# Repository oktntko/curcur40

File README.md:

# curcur40

**curcur40** は、[Corne Keyboard (crkbd v4)](https://github.com/foostan/crkbd) をベースに、Kailh Choc V2（`CPG1353`）ロープロファイルスイッチ専用の **40キー左右分割レイアウト**、右手親指内側の **$\varnothing 25\,\text{mm}$ 光学式トラックボール（`PMW3360DM-T2QU` 低プロファイル分離センサーサブ基板）**、および右手人差し指内側の **アンダープレート 1ピース一体軸パッシブ磁気慣性ホイール（`45# Steel` 削り出しフライホイール ＋ 右メイン基板 PCBA 直実装 `TMAG5273` 3Dホール磁気センサ）** を統合し、筐体全体を **真鍮ヒートセットインサート × 統一 `M2 × 6.0mm` ネジ（100% 密閉・底面穴なしケース）** で構築したカスタム分割エルゴノミクスキーボードです。

---

## 主な特徴 (Key Features)

- **40キー + 25mm トラックボール + アンダープレート一体軸パッシブ磁気慣性ホイール**:
  - **左手 (21キー)**: メイン $3\times 5$ (15キー) ＋ 内側縦2キー (`EXSW1`, `EXSW2`) ＋ 親指4キー (`SW1`, `SW8`, `SW9`, `EXSW3`)
  - **右手 (19キー + 2デバイス)**: メイン $3\times 5$ (15キー) ＋ 内側下段1キー (`rEXSW2`) ＋ 親指外側3キー (`rSW1`, `rSW8`, `rSW9`) ＋ **アンダープレート一体軸パッシブ磁気慣性ホイール（静音中クリック付）** ＋ **$\varnothing 25\,\text{mm}$ トラックボール (`PMW3360DM-T2QU` + `LM19-LSI`)**
- **接着剤ゼロ・シムゼロ・手配線ゼロ・カバー不要の「アンダープレート 1ピース一体軸パッシブ磁気慣性ホイール」**:
  - 指当たりが広く心地よい **外径 $\varnothing 22.00 \times \text{幅 } 6.50\,\text{mm}$ リム（外周24フルート溝、南側キー `rEXSW2` と左右中心軸完全一致）**・$\varnothing 2.90\,\text{mm}$ 内輪当たり段付き肩・$\varnothing 1.98\,\text{mm}$ ジャーナル＆Dカット軸を単一鋼材から削り出した **1ピース `45# Steel`（無電解ニッケルめっき）フライホイール（[`steel-flywheel.step`](./cases/inertia_wheel/steel-flywheel.step), $19.31\,\text{g}$, $J \approx 1160\,\text{g}\cdot\text{mm}^2$）** と脱脂ミニチュアベアリング **`DDL-520ZZ`**（Cクリップスナップイン保持）により、シムリング調整なしで圧倒的な慣性フリースピンと剛性を実現。
  - 回転軸をプレート下（$Z = -6.90\,\text{mm}$）に沈めることで、大径 $\varnothing 22.00\,\text{mm}$ ホイールでありながら頂点高さを **$Z = +4.10\,\text{mm}$（Choc V2 キーキャップ天面 $+3.60\,\text{mm}$ 比わずか $+0.50\,\text{mm}$）** に抑え、トッププレート開口をカバー不要のシンプルな角丸長穴（$7.70 \times 22.00\,\text{mm}$）に集約。
  - 角度検出には右メイン基板 `B.Cu` へ PCBA 自動実装された 3軸リニアホールIC **`rU6`（`TMAG5273A1QDBVR`）**、中クリックには基板直付けの静音スイッチ **`rEXSW1`（`Kailh Square Silent`）** を採用し、さらに `#03` シーソーロッカーと `#04` クレードルを **Cクリップスナップインヒンジ（抱き角 $239^\circ$）** で機械連結（**ホイール用サブ基板・JST SH コネクタ・手配線ハーネスは完全廃止**）。南ボスの鉄製 `M2×6.0mm` ネジ先端に自己磁力で吸着させた $\varnothing 2\times 2\,\text{mm}$ ネオジム磁石（`NE280`）と強磁性スチールホイールの24溝により、接着剤も鋼球ハブも使わずにノッチ強弱を無段階調整可能。
- **全19箇所 真鍮ヒートセットインサート ＆ 統一 `M2 × 6.0mm` ネジ（左右完全対称キー谷間 $\varnothing 5.20\,\text{mm}$ フラットボス・USB-C 内壁基板受け棚・スイッチ嵌合トッププレート ＆ 100% 密閉フラット底面ケース）**:
  - 旧来の `5.50mm` スペーサーおよびケース底面ザグリ穴を全面廃止し、キーボード全体の全19箇所（左手キー谷間 `L1`〜`L6` 6箇所 ＋ 右手キー谷間 `R1`〜`R6` 6箇所 ＋ トラックボールカップ `TB1`〜`TB4` 4箇所 ＋ ホイールクレードル `WC1`/`WC2` 2箇所 ＋ ホイール磁力調整 1箇所）すべてを **`M2 × L=3.0 × OD=3.2mm` 真鍮ヒートセットインサート（19個）** と **同一サイズの `M2 × 6.0mm` ネジ（19本）** に完全統一。
  - 左右のメイン基板固定穴は、外周余白で目立っていたネジ穴を全廃し、**左右完全対称のキー間谷間・死角 6点ずつ（計12箇所：`L1`〜`L6` および `R1`〜`L6`）** へ再配置。すべて **段差ゼロのコンパクトな $\varnothing 5.20\,\text{mm}$ 単段フラット円筒ボス（天面 $Z = -5.80\,\text{mm}$、片側均一肉厚 $1.175\,\text{mm}$）** に統一し、さらに USB-C ポート近傍のケース内壁死角に一体成形した **3箇所の基板受け棚（$Z = -5.80\,\text{mm}$）** がケーブル挿抜時の下向き荷重を強固に支持します。トッププレートは全14箇所を $\varnothing 4.40\,\text{mm}$ ネジ頭逃げ穴としてネジ頭をプレート下に沈み込ませ、40個の Kailh Choc V2 キースイッチ嵌合でスマートに保持されます（KiCad 10.0 実3D部品モデル全535個＋嵌合 JST `SHR-06V-S-B` ハウジング2個を統合した全674ソリッドの干渉ゼロ＆全パーツ6自由度拘束を自動検証済み）。
  - 普通のはんだごて（220〜250℃）で PA12 ナイロンケースの下穴（$\varnothing 2.85\,\text{mm}$）へインサートを押し込む片側上方向締結により、ケース外底面は **ネジ穴・ザグリ穴が一切ない 100% 密閉フラット底面**（ビルトインテンティング角 $\theta_{\text{tent}} = 7.47^\circ$：小指端全高 $10.00\,\text{mm}$ 〜 親指端全高 $26.90\,\text{mm}$）を実現。
- **低プロファイル沈み込み 25mm トラックボール**:
  - トラックボールカップの円形リム天面をトッププレート表面（$Z = -2.00\,\text{mm}$）と同一平面に揃えて $-11.80\,\text{mm}$ 低プロファイル化。PMW3360 回路を独立サブ基板 [`curcur40-pmw3360`](./pcbs/pmw3360/curcur40-pmw3360.kicad_pcb)（$Z = -16.00\,\text{mm}$）に分離し、右メイン基板 `rJ3` とセンサー基板 `J1` を JST SH 6ピン両端同方向フラットケーブル1本で接続。
  - $\varnothing 2.0\,\text{mm}$ セラミック球 3点支持と T字スリム3爪（スロート径 $\varnothing 24.59\,\text{mm}$）により、滑らかな回転と逆さ落下防止を両立。
- **RP2040 オンボード & デュアル USB-C・複合ポインティング搭載 QMK / Vial 完全対応**:
  - 左右とも `RP2040` + `16MB` QSPI Flash をオンボード実装し、PC接続（北側 `J1`/`rJ1`）および左右間接続（親指内側 `J2`/`rJ2`、ESD保護・コールドソケット誤挿し保護搭載）ともに USB Type-C を採用。
  - ファームウェアには **`TMAG5273` 3Dホール慣性ホイール駆動**（`XZX` 擬似同時サンプリングで高速スピン位相遅れを解消、物理24溝と同期した `24 notches/rev`、`TLV493D-A1B6` 自動フォールバック、`WHL_HRZ` 水平スクロール切替対応［`Shift` 併用時は標準の OS 側 `Shift + 縦スクロール` 挙動に委譲］）と **`PMW3360` トラックボールの 2D 慣性高速ドラッグスクロール** を統合し、Vial GUI からリアルタイムに設定変更可能。

---

## ドキュメント・設計仕様書 (Documentation)

| ドキュメント | 内容 |
| :--- | :--- |
| **[ビルドガイド (`docs/buildguide_jp.md`)](./docs/buildguide_jp.md)** | 必要パーツ一覧（BOM）、JLCPCB / JLC3DP / JLCCNC 発注手順、真鍮ヒートセットインサート圧入、慣性ホイール＆トラックボール組立、ファームウェア書き込み手順 |
| **[購入部材・製造委託パーツリファレンス (`docs/parts_spec.md`)](./docs/parts_spec.md)** | ベアリング（`DDL-520ZZ`）・磁石（`D4×1mm`, `NE280`）・静音スイッチ・真鍮インサート・統一 `M2×6mm` ネジ・委託造形品の確定型番と購入先URL一覧 |
| **[ケース・機構設計仕様書 (`docs/case_spec.md`)](./docs/case_spec.md)** | Z軸スタックアップ定義、19箇所真鍮ヒートセットインサート＋統一 `M2×6.0mm` ネジ締結仕様、USB-C内壁基板受け棚、100%密閉底面ケース、トラックボールカップ＆光学距離（$2.40\,\text{mm}$）仕様、持ち運び用上下リバーシブル・キャリングボックス仕様 |
| **[PCB・回路図設計仕様書 (`docs/pcb_spec.md`)](./docs/pcb_spec.md)** | 全3基板（`left`, `right`, `pmw3360`）の回路構成、オンボード3Dホール `rU6` (`TMAG5273`) ＆ `rEXSW1` 仕様、RP2040 GPIO ピンアサイン表、DRC/ERC 検証基準 |
| **[パッシブ磁気慣性ホイール設計仕様書 (`docs/passive_inertia_wheel_spec.md`)](./docs/passive_inertia_wheel_spec.md)** | **小学生でもわかる「3つのしくみ」図解**、幅 $6.50\,\text{mm}$ 一体軸 `45# Steel` ホイールの物理設計、接着剤ゼロ磁気デテント＆Cクリップシーソー中クリック機構、6自由度拘束検証、`XZX` 3Dホール角度復調アルゴリズム |
| **[さわって動かせる！3つのしくみインタラクティブ図解 (`docs/wheel_mechanism_guide.html`)](./docs/wheel_mechanism_guide.html)** | ブラウザでオフライン動作する体験型 HTML ガイド（ホイールのフリック高速スピン、ノッチ調整ネジスライダー、Cクリップシーソー中クリックを実際に操作可能） |
| **[まっすぐ引くだけでフタが抜けるしくみ図解 (`docs/carrying_box_lid_guide.html`)](./docs/carrying_box_lid_guide.html)** | ブラウザでオフライン動作する体験型 HTML ガイド（キャリングボックスの $26^\circ$ 浅角カム坂道・$14\,\text{mm}$ 長スパン弾性梁によるスナップフタ開閉動作をスライダーで操作可能） |
| **[生成スクリプト一覧 (`scripts/README.md`)](./scripts/README.md)** | 3Dモデル（ケース・カップ・慣性ホイール・キャリングボックス・フルアセンブリ）、トッププレート、JLCPCB 発注データ、図版・プレビュー画像・3D組み立てアニメーション動画の再現生成スクリプト（全12本）の説明 |

---

## 3D プレビュー・完成イメージギャラリー (3D Preview Gallery)

KiCad 10.0 Raytracing（`kicad-cli pcb render`）、`cadgen` 3D CAD レンダラー、および PyVista PBR レンダラーで出力した完成イメージ・組み立て動画一覧です。

- 🎬 **[3D 組み立てアニメーション動画 (`docs/assets/assembly_animation.mp4`, 1080p 60fps)](./docs/assets/assembly_animation.mp4)** — トラックボールユニット ＆ パッシブ磁気慣性ホイールのサブ組立から、白ケース・黒PCB・黒トッププレート・スイッチ・白キーキャップ・25mmボールの積み上げ完成までを収録した PBR 3D 動画

### 1. フルアセンブリ（密閉底面3Dプリントケース + メイン基板 + トッププレート + 25mmトラックボール + アンダープレート一体軸慣性ホイール）

#### 斜視図（アイソメトリックビュー）

#### 上面図（トップビュー：カバー不要のスマートなホイールスロット＆ネジ頭沈み込みプレート）

#### 底面図（ボトムビュー：ネジ穴・ザグリ穴ゼロの 100% 密閉フラットケース底面）

---

### 2. 左手メイン基板 (`curcur40-left`)
- **構成**: 21キー（メイン $3\times 5$ + 内側 1u×2 + 親指 1u×4）、板厚 `1.60 mm` 裏面 PCBA
- **制御回路**: `RP2040` + `W25Q128JVSIQ` (16MB) + デュアル USB Type-C（北側 `J1`・内側 `J2`、ESD保護・逆流防止ダイオード搭載）
- **基板固定構造**: 左右完全対称のキー谷間6箇所（`L1`〜`L6`、外周余白穴ゼロ）すべてシンプルな **$\varnothing 2.40\,\text{mm}$ 円穴**（太穴や南開放U溝なし）とし、ケースの $\varnothing 5.20\,\text{mm}$ フラット円筒ボスへ `M2×6.0mm` ネジで直接締結（USB-C近傍3箇所はケース内壁基板受け棚で下支え）

#### 表面（スイッチ差し込み面 / `F.Cu`）

#### 斜視図 ＆ 裏面（部品実装面 / `B.Cu`）
| 斜視図（アイソメトリックビュー） | 裏面（部品実装面 / `B.Cu`） |
| :---: | :---: |
|  |  |

---

### 3. 右手メイン基板 (`curcur40-right`) ＆ トラックボールセンサーサブ基板 (`curcur40-pmw3360`)
- **構成**: 19キー ＋ **アンダープレート一体軸ホイール十字切り欠き窓 ＆ オンボード `rU6` (`TMAG5273`) / `rEXSW1` (`Kailh Square Silent`)** ＋ **25mm トラックボール光学センサーサブ基板**（`rJ3` ⇔ `J1` JST SH 6ピン接続）
- **サブ基板1枚のみのシンプル構成**:
  - 慣性ホイールの3Dホールセンサー `rU6`（`TMAG5273A1QDBVR`, LCSC `C3716049`）は右メイン基板 `B.Cu` に PCBA 実装され、静音中クリックスイッチ `rEXSW1` も右メイン基板 `B.Cu` に直接ハンダ付けされるため、ホイール用の別基板やハーネスは一切不要です。
  - トラックボール用の [`curcur40-pmw3360`](./pcbs/pmw3360/curcur40-pmw3360.kicad_pcb) のみを $-11.80\,\text{mm}$ 下段（$Z = -17.60 \sim -16.00\,\text{mm}$）に分離し、唯一の JST SH 6ピンケーブル（`rJ3` ⇔ `J1`）で接続します（裏面 `JP1` は銅箔パターンで `+3V3R` 直結済み）。

#### 右メイン基板 表面（`F.Cu`）・斜視図・裏面（`B.Cu`：`rU6`, `rEXSW1`, `rJ3` 搭載）

| 斜視図（アイソメトリックビュー） | 裏面（SMD部品・オンボード `rU6`・`rJ3` 実装面 / `B.Cu`） |
| :---: | :---: |
|  |  |

#### トラックボールセンサーサブ基板 (`curcur40-pmw3360`) プレビュー
| TBセンサー基板 表面 (`F.Cu`) | TBセンサー基板 裏面 (`B.Cu`) |
| :---: | :---: |
|  |  |

---

### 4. FR-4 トッププレート (`plate-top-left` / `plate-top-right`)
- **材質・板厚**: FR-4（ガラスエポキシ基板材）、板厚 $1.60\,\text{mm}$（$Z = -3.60 \sim -2.00\,\text{mm}$）
- **全14箇所 ネジ頭沈み込み逃げ穴（$\varnothing 4.40\,\text{mm}$）＆ スイッチ嵌合保持**: 左6箇所（`L1`〜`L6`）および右8箇所（`R1`〜`R6, WC1, WC2`）の全14箇所すべてをキーキャップ間の死角に配置した **$\varnothing 4.40\,\text{mm}$ ネジ頭逃げ穴** に統一し（外周余白のむき出しネジ穴ゼロ）、`M2×6.0mm` ネジ頭をメイン基板 `F.Cu`（$Z = -4.20\,\text{mm}$）へ着座させてプレート天面（$Z = -2.00\,\text{mm}$）より下に完全沈み込ませています（キー押下時の干渉ゼロ）。プレート自体は Kailh Choc V2 キースイッチ（左21個・右19個）のラッチ嵌合により全周ガタなく保持されます。
- **右手プレート形状**: 南側キー `rEXSW2` と左右中心軸を完全一致させたカバー不要のシンプルな $7.70 \times 22.00\,\text{mm}$（$R = 1.00\,\text{mm}$）幅広ホイール長穴と、親指内側のトラックボールカップ切り欠きを備えたクリーンな造形です。

| 左手トッププレート (`plate-top-left`) | 右手トッププレート (`plate-top-right`) |
| :---: | :---: |
|  |  |

---

### 5. トラックボールカップ ＆ アンダープレート一体軸パッシブ磁気慣性ホイール
5つの光学・フルアセンブリ STEP モデルには、GUI（CAD Viewer等）で 25mm ボール底面との規定光学距離（設計値 **$2.40\,\text{mm}$**）を直接計測できるよう独立オブジェクト **`Lens_Optical_Ref_Point`** が収録されています。

| トラックボールカップ単体 (`cases/trackball-cup.step`) | 25mmボール・レンズ組込 (`cases/assemblies/trackball-cup-with-ball.step`) |
| :---: | :---: |
|  |  |

| 右手アンダープレート慣性ホイール実装 (`curcur40-right-wheel-assembly.step`) | アンダープレート一体軸ホイール機構単体 (`inertia-wheel-assembly.step`) |
| :---: | :---: |
|  |  |

#### 小学生でもわかる！高速スクロールホイールの「3つのしくみ」と `#02` の場所
> 💡 ブラウザで実際にホイールを弾いたりネジ・クリックを動かして遊べる **[インタラクティブ HTML 版 (`docs/wheel_mechanism_guide.html`)](./docs/wheel_mechanism_guide.html)** も収録しています。

---

### 6. 持ち運び用キャリングボックス（オプション：上下リバーシブル・スナップフタ付き6面フルカバー）
左右ケースの $7.47^\circ$ ビルトインテンティング傾斜を互い違いの向き（左手を $X$ 軸まわりに $180^\circ$ 反転）で対面させて相殺し、**$\varnothing 8 \times 2\,\text{mm}$ ゴム足 10 個・25mm トラックボール・全 4 箇所の USB-C マグネット端子（`CIO-SLMG-T-C`）を装着したまま** 真の $90^\circ$ 直方体ブロックとして安全に持ち運べる `PA12` キャリングボックス（[`carrying-box.step`](./cases/carrying-box.step) ＋ [`carrying-box-lid.step`](./cases/carrying-box-lid.step)）を用意しています。

- **箱もフタも上下逆さま区別なし（高さ増加ゼロの完全点対称 $142.40 \times 111.85 \times 65.42\,\text{mm}$）**: 点対称クランク段差ディバイダ＋左右デュアル 25mm 球キーパー溝により、**右手トラックボール側を下にしても上にしても（箱・フタの上下向きを一切見ずに）そのままスッと差し込んで閉められます**。全10個のゴム足は常時 $0.75\,\text{mm}$ 空中に浮き、奥面とフタ内面には外へ貫通しない **デュアル内部「堀」＋ キーボード手前突き当たりストッパー段差** を備えています。
- **力学計算済みの長スパン $26^\circ$ 浅角カム式隠しスナップフタ**: 長さ $14.0\,\text{mm}$ の弾性梁と抜き角 $26^\circ$ の浅角カムにより偏心セルフロックを完全解消し、左右の指掛け溝を持って真っ直ぐ引くだけで **約 $9.7\,\text{N}$（約 $1.0\,\text{kgf}$、最大曲げひずみ $0.71\%$）** でスムーズに開閉できます。

> 💡 まっすぐ引っ張るだけでスナップフタが抜けるしくみをスライダーで体験できる **[インタラクティブ HTML 図解 (`docs/carrying_box_lid_guide.html`)](./docs/carrying_box_lid_guide.html)** も収録しています。

| フタ装着フルカバー収納 (`carrying-box-with-lid-assembly.step`) | フタ取り外し・スライド挿入時 (`carrying-box-assembly.step`) |
| :---: | :---: |
|  |  |

| ボックス単体 (`cases/carrying-box.step`) | 差込口正面（ゴム足フローティング＆中央 TB キーパー断面視） |
| :---: | :---: |
|  |  |

---

## リポジトリ構成と発注用データ (Repository Structure & Production Files)

```text
curcur40/
├── cases/                        # 3Dプリント・CNC切削用実部品 & 検証アセンブリ (STEP / STL)
│   ├── left.step / left.stl      # 左手密閉底面ボトムケース（トッププレート水平基準）
│   ├── left-desk.step / .stl     # 左手密閉底面ボトムケース（ケース外底面＝デスク水平基準・JLC3DP推奨）
│   ├── right.step / right.stl    # 右手密閉底面ボトムケース（トッププレート水平基準）
│   ├── right-desk.step / .stl    # 右手密閉底面ボトムケース（ケース外底面＝デスク水平基準・JLC3DP推奨）
│   ├── trackball-cup.step / .stl # 25mmトラックボール用スナップインカップ（2.0mmフラット固定耳）
│   ├── carrying-box.step / .stl      # 【オプション】持ち運び用上下リバーシブル直方体スライドボックス本体 (JLC3DP PA12)
│   ├── carrying-box-lid.step / .stl  # 【オプション】スライドボックス用上下リバーシブル・スナップフタ (JLC3DP PA12)
│   ├── inertia_wheel/            # アンダープレート一体軸慣性ホイール実部品 4種
│   │   ├── steel-flywheel.step/.stl  # #01 1ピース一体軸 45# Steel + 無電解Ni ホイール (JLCCNC)
│   │   ├── magnet-holder.step/.stl   # #02 接着剤ゼロ D4×1mm 磁石ホルダー (JLC3DP PA12)
│   │   ├── wheel-rocker.step/.stl    # #03 一体トラニオン軸シーソーロッカー (JLC3DP PA12)
│   │   └── wheel-cradle.step/.stl    # #04 Cクリップスナップインヒンジ付アンダーPCBクレードル (JLC3DP PA12)
│   └── assemblies/               # 光学距離・干渉・クリアランス検証用アセンブリモデル 9種 (STEP / STL)
│       ├── assembly-full.step                    # KiCad実3D部品535個同期・全674ソリッド統合フルアセンブリ（トッププレート水平基準）
│       ├── assembly-full-desk.step               # KiCad実3D部品535個同期・全674ソリッド統合フルアセンブリ（ケース底面＝デスク面 Z=0 基準）
│       ├── carrying-box-assembly.step            # スライドボックス収納検証アセンブリ・フタ取り外し内部確認用（全689ソリッド）
│       ├── carrying-box-with-lid-assembly.step   # スライドボックス収納フルアセンブリ・フタ装着標準姿勢（全690ソリッド）
│       ├── curcur40-right-wheel-assembly.step    # 右手＋KiCad実3D部品＋アンダープレート慣性ホイール検証アセンブリ（349ソリッド）
│       ├── inertia-wheel-assembly.step           # アンダープレート慣性ホイール機構単体アセンブリ（14パーツ）
│       ├── trackball-cup-with-ball.step/.stl     # カップ＋25mm球＋光学基準点アセンブリ
│       ├── pmw3360-lens-pcb-assembly.step        # PMW3360＋LM19レンズ＋サブ基板光学モジュール
│       └── trackball-sensor-assembly.step        # カップ＋25mm球＋センサーサブ基板統合アセンブリ
├── pcbs/                         # KiCad 10.0 全3基板 (すべて 1.6mm Bottom PCBA) & JLCPCB 発注データ
│   ├── left/                     # 左手メイン基板 (curcur40-left)
│   ├── right/                    # 右手メイン基板 (curcur40-right: オンボード rU6 TMAG5273 & rEXSW1 搭載)
│   ├── pmw3360/                  # トラックボールセンサーサブ基板 (curcur40-pmw3360)
│   └── common/kbd/               # プロジェクト固有 KiCad シンボル・フットプリント・3Dモデルライブラリ
├── plates/                       # FR-4 トッププレート KiCad PCB / Gerber & レーザーカット用 SVG
│   ├── pcb/                      # plate-top-left.kicad_pcb, plate-top-right.kicad_pcb
│   └── svg/                      # plate-curcur40.svg, foam-curcur40.svg
├── kbd_firmware/                 # QMK / Vial ファームウェアソース (keyboards/curcur40)
├── docs/                         # ビルドガイド・設計仕様書・購入部材リファレンス・体験型HTML・図版アセット
│   ├── buildguide_jp.md
│   ├── parts_spec.md
│   ├── case_spec.md
│   ├── pcb_spec.md
│   ├── passive_inertia_wheel_spec.md
│   ├── wheel_mechanism_guide.html
│   ├── carrying_box_lid_guide.html
│   └── assets/
└── scripts/                      # 3Dモデル・プレート・JLCPCBデータ・プレビュー画像の公式生成スクリプト群（12本）
```

---

## ライセンス・謝辞 (License & Credits)

本プロジェクトは、以下のオープンソースハードウェア／ソフトウェアプロジェクトの成果をベースに派生・統合して作成されています。各オリジナル作者の皆様に深く感謝いたします。

| 対象領域 / ファイル | 派生元リポジトリ・原著作者 | 適用ライセンス | 改変履歴・表示事項（CC BY 4.0 Sec. 3(a) / CERN-OHL-P v2 Sec. 3.3 準拠） |
| :--- | :--- | :--- | :--- |
| **基板・プレート・ケース・慣性ホイール・ドキュメント・スクリプト**<br>(`pcbs/`, `plates/`, `cases/`, `docs/`, `scripts/`) | **[foostan/crkbd](https://github.com/foostan/crkbd)**<br>(Original Author: `foostan` / Kosuke Adachi) | **[MIT License](./LICENSE_MIT)** ＆<br>**[CC BY 4.0](./LICENSE_CC)** | Corne v4 (`corne-chocolate`) をベースに、40キー配列化・親指クラスタ再配置・右手 PMW3360 トラックボール（低プロファイルサブ基板分離）＆アンダープレート一体軸パッシブ磁気慣性ホイール（`45# Steel` ロータ + オンボード `TMAG5273` 3Dホール）統合・KiCad 10.0 対応・ヒートセット密閉底面3Dプリントケース＆トラックボールカップ新規設計を実施（`2026-10`） |
| **プロジェクト固有 KiCad ライブラリ（Corne 由来）**<br>(`pcbs/common/kbd/kicad-symbols/kbd.kicad_sym`, `kbd.pretty/`, `kicad-packages3D/kbd.3dshapes/`) | **[foostan/kbd](https://github.com/foostan/kbd)**<br>(Original Author: `foostan`) | **[MIT License](./pcbs/common/kbd/LICENSE)** | `2026-10`: 未使用シンボル・フットプリント・3Dモデルを整理し、KiCad 10.0 標準シンボルとのピン名・フィルタ整合、`YS-SK6812MINI-E` Pin 2 (`DOUT`) 電気タイプ修正、`keyswitch_choc12_hotswap_1u` の旧 $\varnothing 0.40\,\text{mm}$ NPTH 穴削除、`Kailh_Square_Silent_6.2x6.2mm` 追加、環境非依存の相対パス化を実施 |
| **PMW3360 回路図シンボル・フットプリント**<br>(`pcbs/common/kbd/kicad-symbols/pmw3360_pcb.kicad_sym`, `PMW3360DM-T2QU_16Pin.kicad_mod`) | **[siderakb/pmw3360-pcb](https://github.com/siderakb/pmw3360-pcb)**<br>(Original Author: `siderakb` / `ziteh`) | **[CERN-OHL-P v2](./LICENSE_CERN_OHL_P_V2)**<br>(Permissive) | `2026-10`: 未使用の `TXS0108E-QPWRQ1` シンボルを削除、`PMW3360DM-T2QU` Pin 3 (`VDDPIX`) を `power_out` に変更、および `PMW3360DM-T2QU_16Pin.kicad_mod` のスルーホールパッド層定義を KiCad 10.0 向けに補完し専用センサーサブ基板 `curcur40-pmw3360` へ統合 |
| **ファームウェア定義 (`kbd_firmware/`)**<br>(`kbd_firmware/keyboards/curcur40/`) | **[foostan/kbd_firmware](https://github.com/foostan/kbd_firmware)**<br>**[QMK Firmware](https://github.com/qmk/qmk_firmware)** / **[Vial-QMK](https://github.com/vial-kb/vial-qmk)** | **GPL-2.0-or-later**<br>(`SPDX-License-Identifier: GPL-2.0-or-later`) | `crkbd/rev4_1/mini` の設定をベースに、40キーマトリックス、I2C0 `TMAG5273`/`TLV493D-A1B6` 3Dホール慣性ホイール＆SPI1 `PMW3360` トラックボール（1200 CPI・2D慣性ドラッグスクロール対応）複合ポインティングドライバへ改変 |

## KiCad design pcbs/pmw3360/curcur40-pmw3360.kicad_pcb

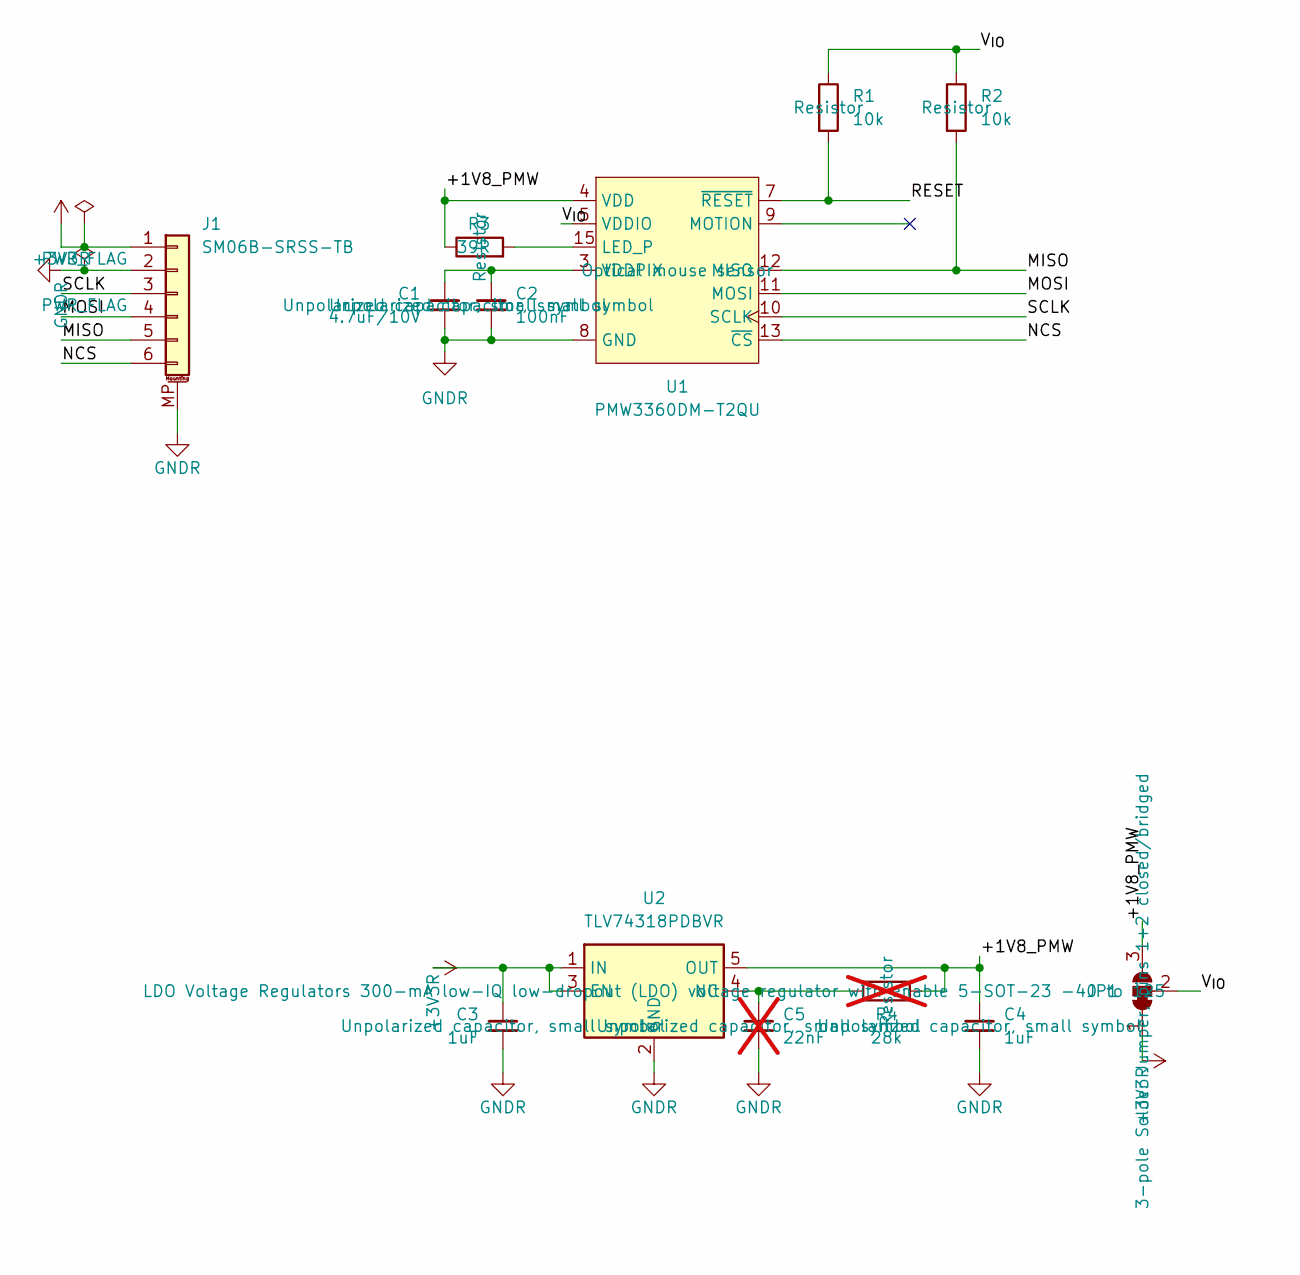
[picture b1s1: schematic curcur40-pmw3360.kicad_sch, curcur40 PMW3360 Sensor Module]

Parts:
C1: 4.7uF/10V; C_0603_1608Metric_Pad1.08x0.95mm_HandSolder; Mfr. # CL10A475KO8NNNC; LCSC C19666
C2: 100nF; C_0603_1608Metric_Pad1.08x0.95mm_HandSolder; Mfr. # CC0603KRX7R9BB104; LCSC C14663
C3, C4: 1uF; C_0603_1608Metric_Pad1.08x0.95mm_HandSolder; Mfr. # CL10A105KB8NNNC; LCSC C15849
C5: 22nF; C_0603_1608Metric_Pad1.08x0.95mm_HandSolder; Mfr. # CL10B223KB8NNNC; LCSC C21122; not fitted
J1: SM06B-SRSS-TB; JST_SH_SM06B-SRSS-TB_1x06-1MP_P1.00mm_Horizontal; LCSC C160405
JP1: SolderJumper_3_Bridged12; SolderJumper-3_P1.3mm_Bridged12_RoundedPad1.0x1.5mm_NumberL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
R1, R2: 10k; R_0603_1608Metric_Pad0.98x0.95mm_HandSolder; Mfr. # 0603WAF1002T5E; LCSC C25804
R3: 39R; R_0603_1608Metric_Pad0.98x0.95mm_HandSolder; Mfr. # 0603WAF390JT5E; LCSC C23154
R4: 28k; R_0603_1608Metric_Pad0.98x0.95mm_HandSolder; not fitted
U1: PMW3360DM-T2QU; PMW3360DM-T2QU_16Pin
U2: TLV74318PDBVR; SOT-23-5; Mfr. # TLV74318PDBVR; LCSC C485152

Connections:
+3V3R: C3.1, J1.1, JP1.1 (A), U2.1 (IN), U2.3 (EN)
/+1V8_PMW: C4.1, JP1.3 (B), R3.1, R4.1, U1.4 (VDD), U2.5 (OUT)
/MISO: J1.5, R2.2, U1.12 (MISO)
/MOSI: J1.4, U1.11 (MOSI)
/NCS: J1.6, U1.13 (~CS)
/RESET: R1.2, U1.7 (~RESET)
/SCLK: J1.3, U1.10 (SCLK)
/V_{IO}: JP1.2 (C), R1.1, R2.1, U1.5 (VDDIO)
GNDR: C1.2, C2.2, C3.2, C4.2, C5.2, J1.2, J1.MP (MountPin), U1.8 (GND), U2.2 (GND)
unnamed: R3.2, U1.15 (LED_P)
unnamed: C1.1, C2.1, U1.3 (VDDPIX)
unnamed: C5.1, R4.2, U2.4 (NC)

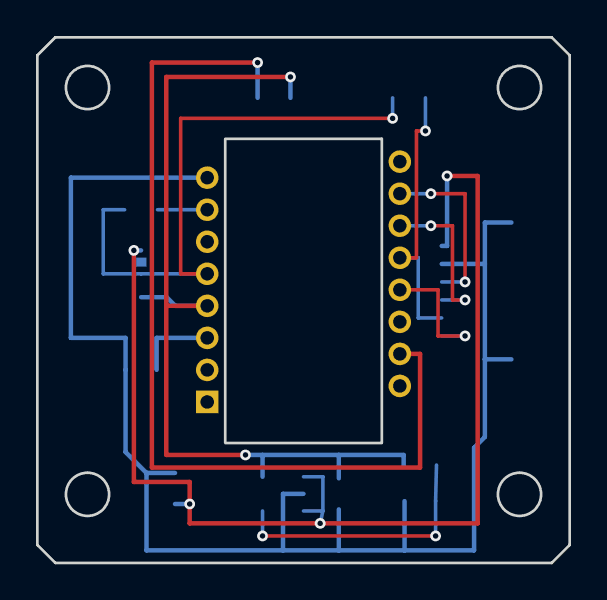
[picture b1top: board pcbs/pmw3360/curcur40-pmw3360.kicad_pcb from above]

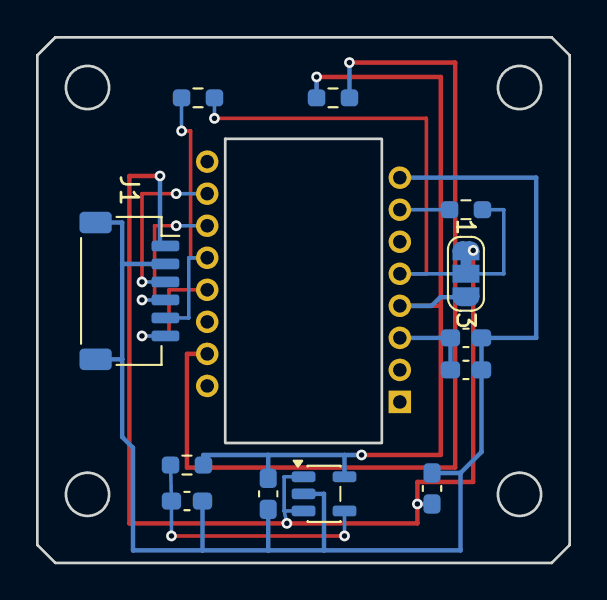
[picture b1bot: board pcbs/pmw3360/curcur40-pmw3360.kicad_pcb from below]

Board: 2 copper layers, 29.6 x 29.2 mm, 13 parts (13 on the bottom side), 12 nets.

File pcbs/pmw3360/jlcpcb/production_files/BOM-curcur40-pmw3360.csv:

Comment,Designator,Footprint,LCSC
100nF,C2,C_0603_1608Metric,C14663
1uF,"C3,C4",C_0603_1608Metric,C15849
SM06B-SRSS-TB(LF)(SN),J1,JST_SH_SM06B-SRSS-TB_1x06-1MP_P1.00mm_Horizontal,C160405
4.7uF/10V,C1,C_0603_1608Metric,C19666
39R,R3,R_0603_1608Metric,C23154
10k,"R1,R2",R_0603_1608Metric,C25804
TLV74318PDBVR,U2,SOT-23-5,C485152

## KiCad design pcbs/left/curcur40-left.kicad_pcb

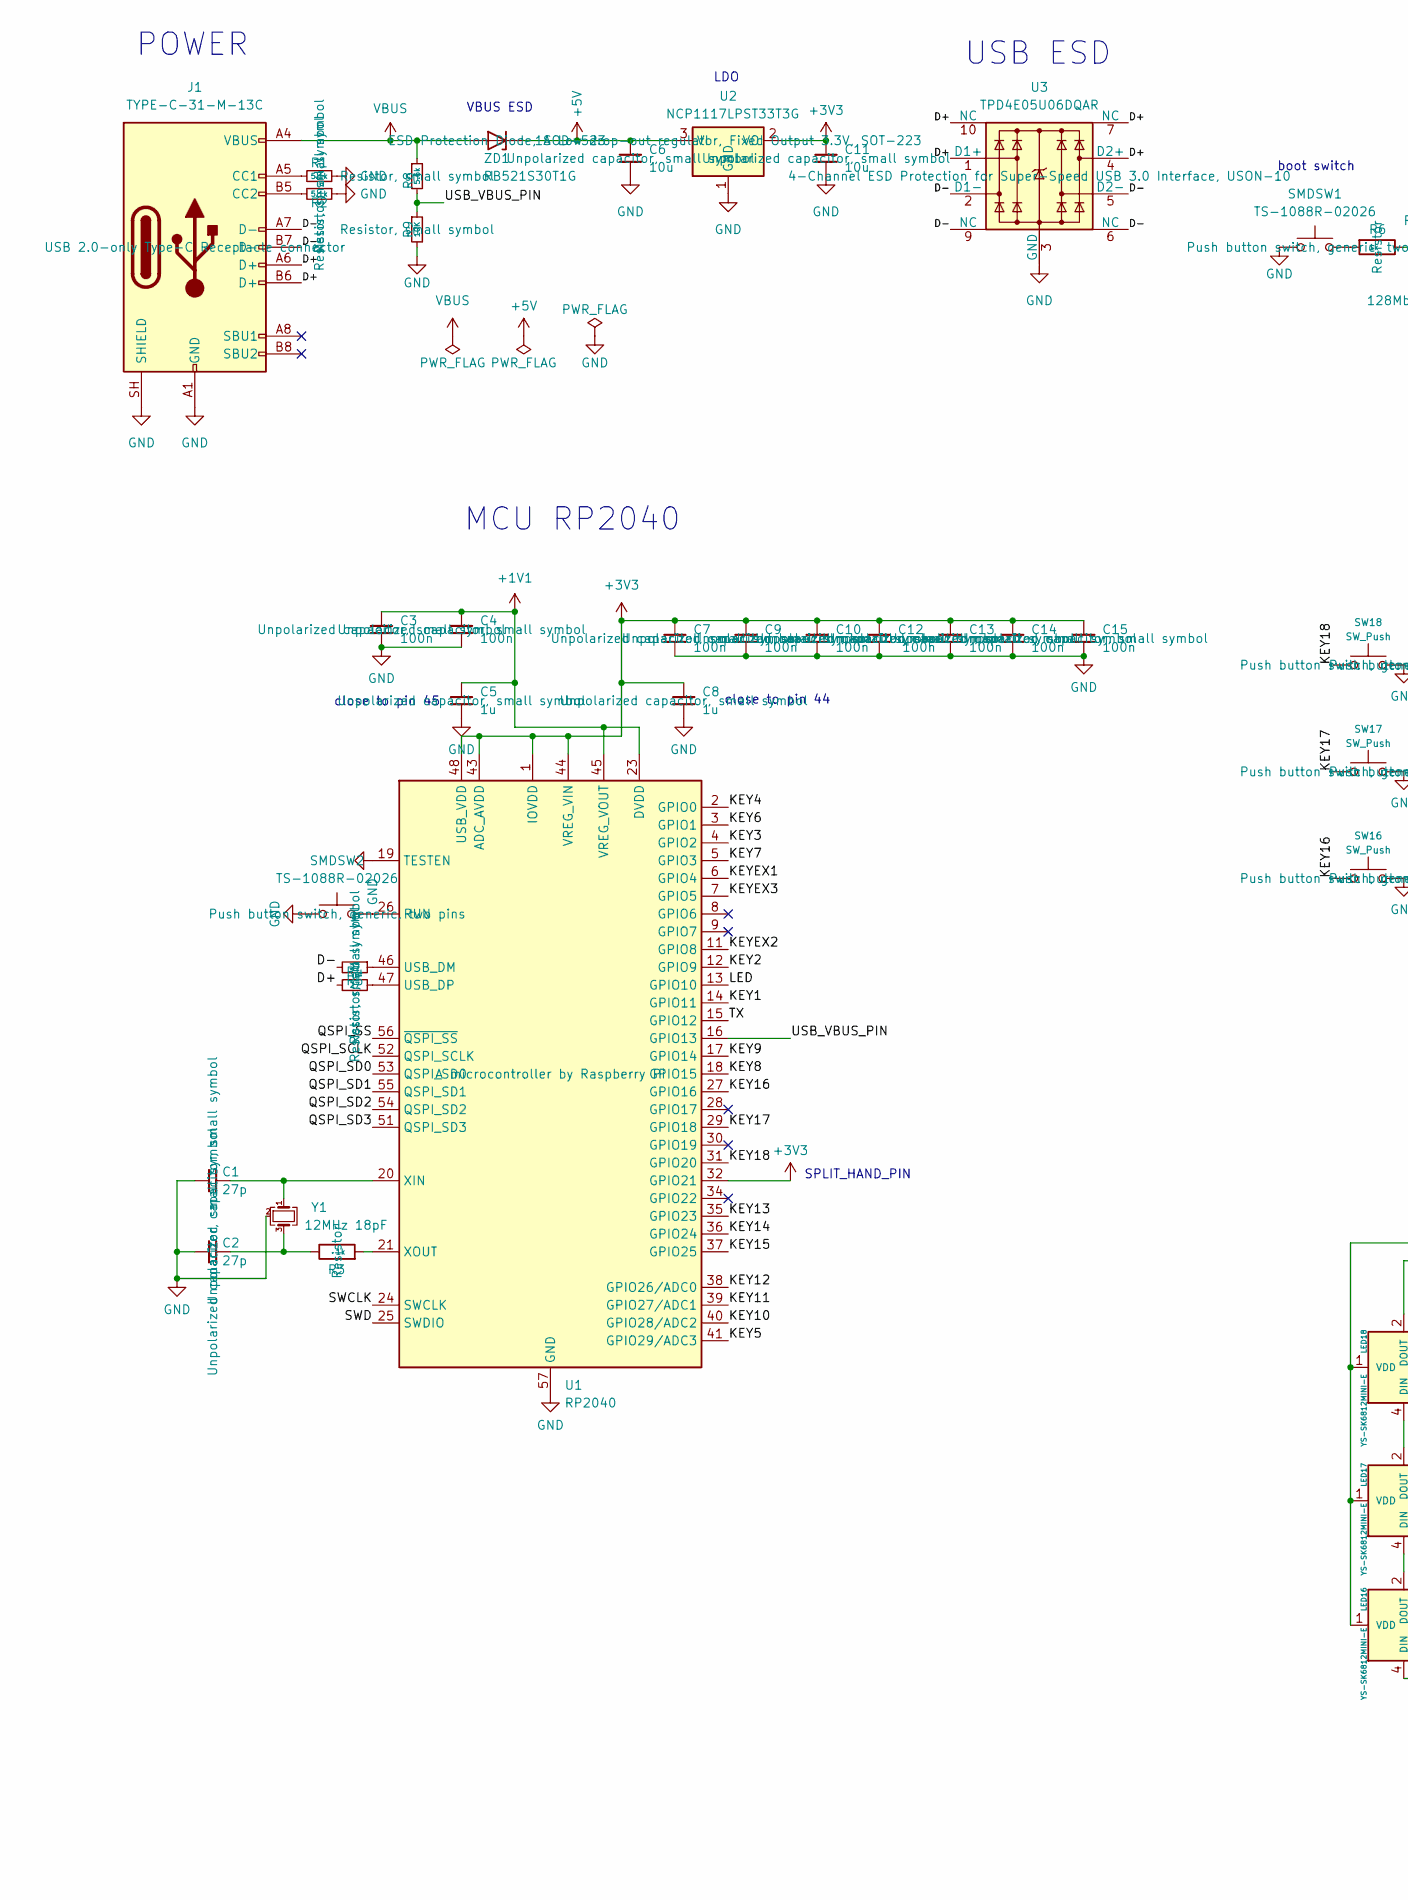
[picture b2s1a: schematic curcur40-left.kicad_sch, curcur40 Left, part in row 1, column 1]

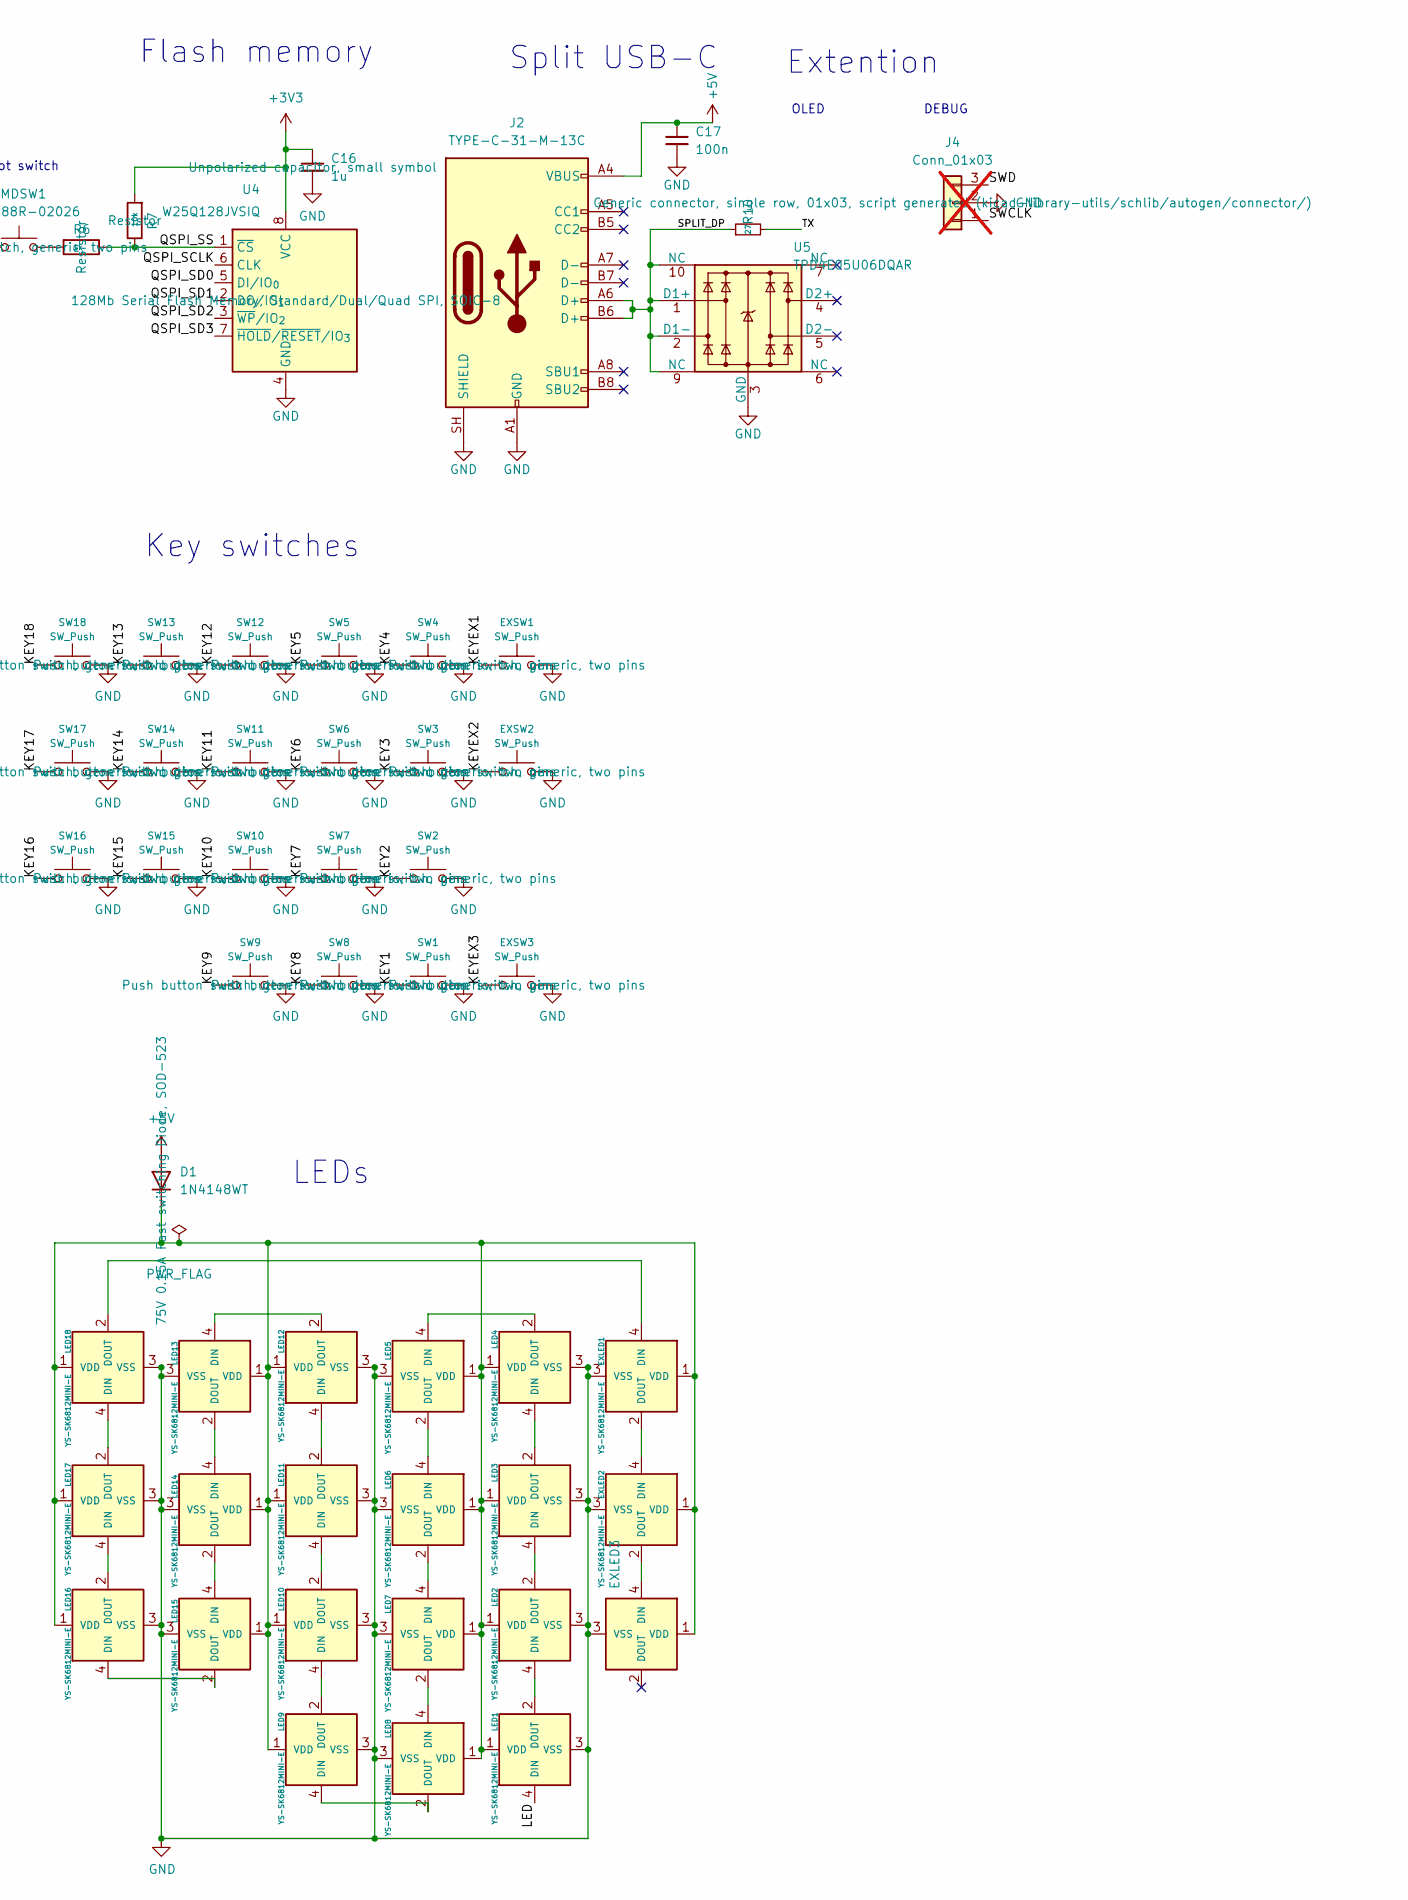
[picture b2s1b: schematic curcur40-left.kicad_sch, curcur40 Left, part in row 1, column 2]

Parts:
C1, C2: 27p; C_0402_1005Metric
C3, C4, C7, C9, C10, C12, C13, C14, C15: 100n; C_0402_1005Metric
C5, C8, C16: 1u; C_0402_1005Metric
C6, C11: 10u; C_0402_1005Metric
C17: 100n; C_0402_1005Metric; JLCPCB Part # C1525
D1: 1N4148WT; D_SOD-523; JLCPCB Part # C232841
EXLED1, EXLED2, EXLED3: YS-SK6812MINI-E
EXSW1, EXSW2, EXSW3: SW_Push; keyswitch_choc12_hotswap_1u
J1, J2: TYPE-C-31-M-13C; USB_C_Receptacle_TYPE-C-31-M-13C; JLCPCB Part # C2848620
J4: Conn_01x03; PinHeader_1x03_P2.54mm_Vertical; not fitted
LED1, LED2, LED3, LED4, LED5, LED6, LED7, LED8, LED9, LED10, LED11, LED12, LED13, LED14, LED15, LED16, LED17, LED18: YS-SK6812MINI-E
R1, R2: 5.1k; R_0402_1005Metric
R3, R6: 1k; R_0402_1005Metric
R4, R5: 27; R_0402_1005Metric
R7: 10k; R_0402_1005Metric
R8: 5.6k; R_0402_1005Metric
R9: 10K; R_0402_1005Metric
R10: 27; R_0402_1005Metric; JLCPCB Part # C2909343
SMDSW1, SMDSW2: TS-1088R-02026; JLCPCB Part # C455280
SW1, SW2, SW3, SW4, SW5, SW6, SW7, SW8, SW9, SW10, SW11, SW12, SW13, SW14, SW15, SW16, SW17, SW18: SW_Push; keyswitch_choc12_hotswap_1u
U1: RP2040; QFN-56-1EP_7x7mm_P0.4mm_EP3.2x3.2mm; JLCPCB Part # C2040
U2: NCP1117LPST33T3G; SOT-223-3_TabPin2; JLCPCB Part # C146799
U3, U5: TPD4E05U06DQAR; USON-10_2.5x1.0mm_P0.5mm; JLCPCB Part # C138714
U4: W25Q128JVSIQ; SOIC-8_5.3x5.3mm_P1.27mm; JLCPCB Part # C113767
Y1: 12MHz 18pF; Crystal_SMD_3225-4Pin_3.2x2.5mm; MFR.Part # Q22FA23V0041800; JLCPCB Part # C91749
ZD1: RB521S30T1G; D_SOD-523; JLCPCB Part # C145179

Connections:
+1V1: C3.1, C4.1, C5.1, U1.23 (DVDD), U1.45 (VREG_VOUT), U1.50 (DVDD)
+3V3: C7.1, C8.1, C9.1, C10.1, C11.1, C12.1, C13.1, C14.1, C15.1, C16.1, R7.2, U1.1 (IOVDD), U1.10 (IOVDD), U1.22 (IOVDD), U1.32 (GPIO21), U1.33 (IOVDD), U1.42 (IOVDD), U1.43 (ADC_AVDD), U1.44 (VREG_VIN), U1.48 (USB_VDD), U1.49 (IOVDD), U2.2 (VO), U4.8 (VCC)
+5V: C6.1, C17.1, D1.2 (A), J2.A4 (VBUS), J2.A9 (VBUS), J2.B4 (VBUS), J2.B9 (VBUS), U2.3 (VI), ZD1.1 (K)
/D+: J1.A6 (D+), J1.B6 (D+), R4.1, U3.1 (D1+), U3.4 (D2+), U3.7 (NC), U3.10 (NC)
/D-: J1.A7 (D-), J1.B7 (D-), R5.2, U3.2 (D1-), U3.5 (D2-), U3.6 (NC), U3.9 (NC)
/KEY1: SW1.1, U1.14 (GPIO11)
/KEY2: SW2.1, U1.12 (GPIO9)
/KEY3: SW3.1, U1.4 (GPIO2)
/KEY4: SW4.1, U1.2 (GPIO0)
/KEY5: SW5.1, U1.41 (GPIO29/ADC3)
/KEY6: SW6.1, U1.3 (GPIO1)
/KEY7: SW7.1, U1.5 (GPIO3)
/KEY8: SW8.1, U1.18 (GPIO15)
/KEY9: SW9.1, U1.17 (GPIO14)
/KEY10: SW10.1, U1.40 (GPIO28/ADC2)
/KEY11: SW11.1, U1.39 (GPIO27/ADC1)
/KEY12: SW12.1, U1.38 (GPIO26/ADC0)
/KEY13: SW13.1, U1.35 (GPIO23)
/KEY14: SW14.1, U1.36 (GPIO24)
/KEY15: SW15.1, U1.37 (GPIO25)
/KEY16: SW16.1, U1.27 (GPIO16)
/KEY17: SW17.1, U1.29 (GPIO18)
/KEY18: SW18.1, U1.31 (GPIO20)
/KEYEX1: EXSW1.1, U1.6 (GPIO4)
/KEYEX2: EXSW2.1, U1.11 (GPIO8)
/KEYEX3: EXSW3.1, U1.7 (GPIO5)
/LED: LED1.4 (DIN), U1.13 (GPIO10)
/QSPI_SCLK: U1.52 (QSPI_SCLK), U4.6 (CLK)
/QSPI_SD0: U1.53 (QSPI_SD0), U4.5 (DI/IO_{0})
/QSPI_SD1: U1.55 (QSPI_SD1), U4.2 (DO/IO_{1})
/QSPI_SD2: U1.54 (QSPI_SD2), U4.3 (~WP/IO_{2})
/QSPI_SD3: U1.51 (QSPI_SD3), U4.7 (~HOLD/~RESET/IO_{3})
/QSPI_SS: R6.1, R7.1, U1.56 (~QSPI_SS), U4.1 (~CS)
/SPLIT_DP: J2.A6 (D+), J2.B6 (D+), R10.1, U5.1 (D1+), U5.2 (D1-), U5.9 (NC), U5.10 (NC)
/SWCLK: J4.1, U1.24 (SWCLK)
/SWD: J4.3, U1.25 (SWDIO)
/TX: R10.2, U1.15 (GPIO12)
/USB_VBUS_PIN: R8.2, R9.1, U1.16 (GPIO13)
GND: C1.2, C2.2, C3.2, C4.2, C5.2, C6.2, C7.2, C8.2, C9.2, C10.2, C11.2, C12.2, C13.2, C14.2, C15.2, C16.2, C17.2, EXLED1.3 (VSS), EXLED2.3 (VSS), EXLED3.3 (VSS), EXSW1.2, EXSW2.2, EXSW3.2, J1.A1 (GND), J1.A12 (GND), J1.B1 (GND), J1.B12 (GND), J1.SH (SHIELD), J2.A1 (GND), J2.A12 (GND), J2.B1 (GND), J2.B12 (GND), J2.SH (SHIELD), J4.2, LED1.3 (VSS), LED2.3 (VSS), LED3.3 (VSS), LED4.3 (VSS), LED5.3 (VSS), LED6.3 (VSS), LED7.3 (VSS), LED8.3 (VSS), LED9.3 (VSS), LED10.3 (VSS), LED11.3 (VSS), LED12.3 (VSS), LED13.3 (VSS), LED14.3 (VSS), LED15.3 (VSS), LED16.3 (VSS), LED17.3 (VSS), LED18.3 (VSS), R1.1, R2.1, R9.2, SMDSW1.1, SMDSW2.1, SW1.2, SW2.2, SW3.2, SW4.2, SW5.2, SW6.2, SW7.2, SW8.2, SW9.2, SW10.2, SW11.2, SW12.2, SW13.2, SW14.2, SW15.2, SW16.2, SW17.2, SW18.2, U1.19 (TESTEN), U1.57 (GND), U2.1 (GND), U3.3 (GND), U3.8 (GND)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
unnamed: C2.1, R3.1, Y1.3
unnamed: D1.1 (K), EXLED1.1 (VDD), EXLED2.1 (VDD), EXLED3.1 (VDD), LED1.1 (VDD), LED2.1 (VDD), LED3.1 (VDD), LED4.1 (VDD), LED5.1 (VDD), LED6.1 (VDD), LED7.1 (VDD), LED8.1 (VDD), LED9.1 (VDD), LED10.1 (VDD), LED11.1 (VDD), LED12.1 (VDD), LED13.1 (VDD), LED14.1 (VDD), LED15.1 (VDD), LED16.1 (VDD), LED17.1 (VDD), LED18.1 (VDD)
unnamed: EXLED1.4 (DIN), LED18.2 (DOUT)
unnamed: EXLED1.2 (DOUT), EXLED2.4 (DIN)
unnamed: EXLED2.2 (DOUT), EXLED3.4 (DIN)
unnamed: J1.A5 (CC1), R1.2
unnamed: J1.B5 (CC2), R2.2
unnamed: LED1.2 (DOUT), LED2.4 (DIN)
unnamed: LED2.2 (DOUT), LED3.4 (DIN)
unnamed: LED3.2 (DOUT), LED4.4 (DIN)
unnamed: LED4.2 (DOUT), LED5.4 (DIN)
unnamed: LED5.2 (DOUT), LED6.4 (DIN)
unnamed: LED6.2 (DOUT), LED7.4 (DIN)
unnamed: LED7.2 (DOUT), LED8.4 (DIN)
unnamed: LED8.2 (DOUT), LED9.4 (DIN)
unnamed: LED9.2 (DOUT), LED10.4 (DIN)
unnamed: LED10.2 (DOUT), LED11.4 (DIN)
unnamed: LED11.2 (DOUT), LED12.4 (DIN)
unnamed: LED12.2 (DOUT), LED13.4 (DIN)
unnamed: LED13.2 (DOUT), LED14.4 (DIN)
unnamed: LED14.2 (DOUT), LED15.4 (DIN)
unnamed: LED15.2 (DOUT), LED16.4 (DIN)
unnamed: LED16.2 (DOUT), LED17.4 (DIN)
unnamed: LED17.2 (DOUT), LED18.4 (DIN)
unnamed: R6.2, SMDSW1.2
unnamed: SMDSW2.2, U1.26 (RUN)
unnamed: R5.1, U1.46 (USB_DM)
unnamed: R4.2, U1.47 (USB_DP)
unnamed: C1.1, U1.20 (XIN), Y1.1
unnamed: R3.2, U1.21 (XOUT)
VBUS: J1.A4 (VBUS), J1.A9 (VBUS), J1.B4 (VBUS), J1.B9 (VBUS), R8.1, ZD1.2 (A)

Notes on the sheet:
MCU RP2040
Key switches
OLED
close to pin 45
DEBUG
USB ESD
LDO
Flash memory
POWER
LEDs
Extention
Split USB-C
VBUS ESD
SPLIT_HAND_PIN
boot switch
close to pin 44

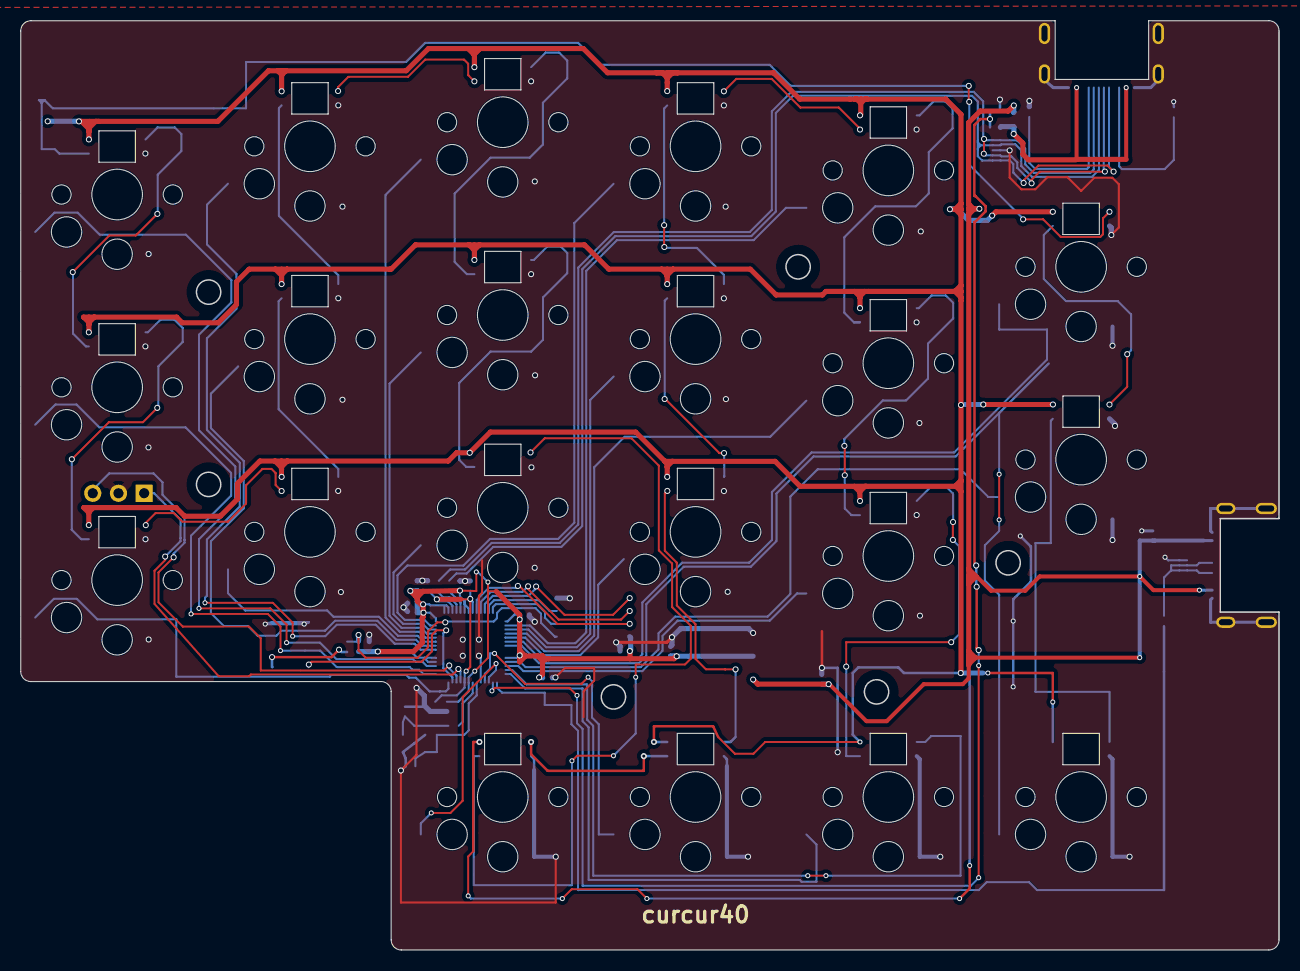
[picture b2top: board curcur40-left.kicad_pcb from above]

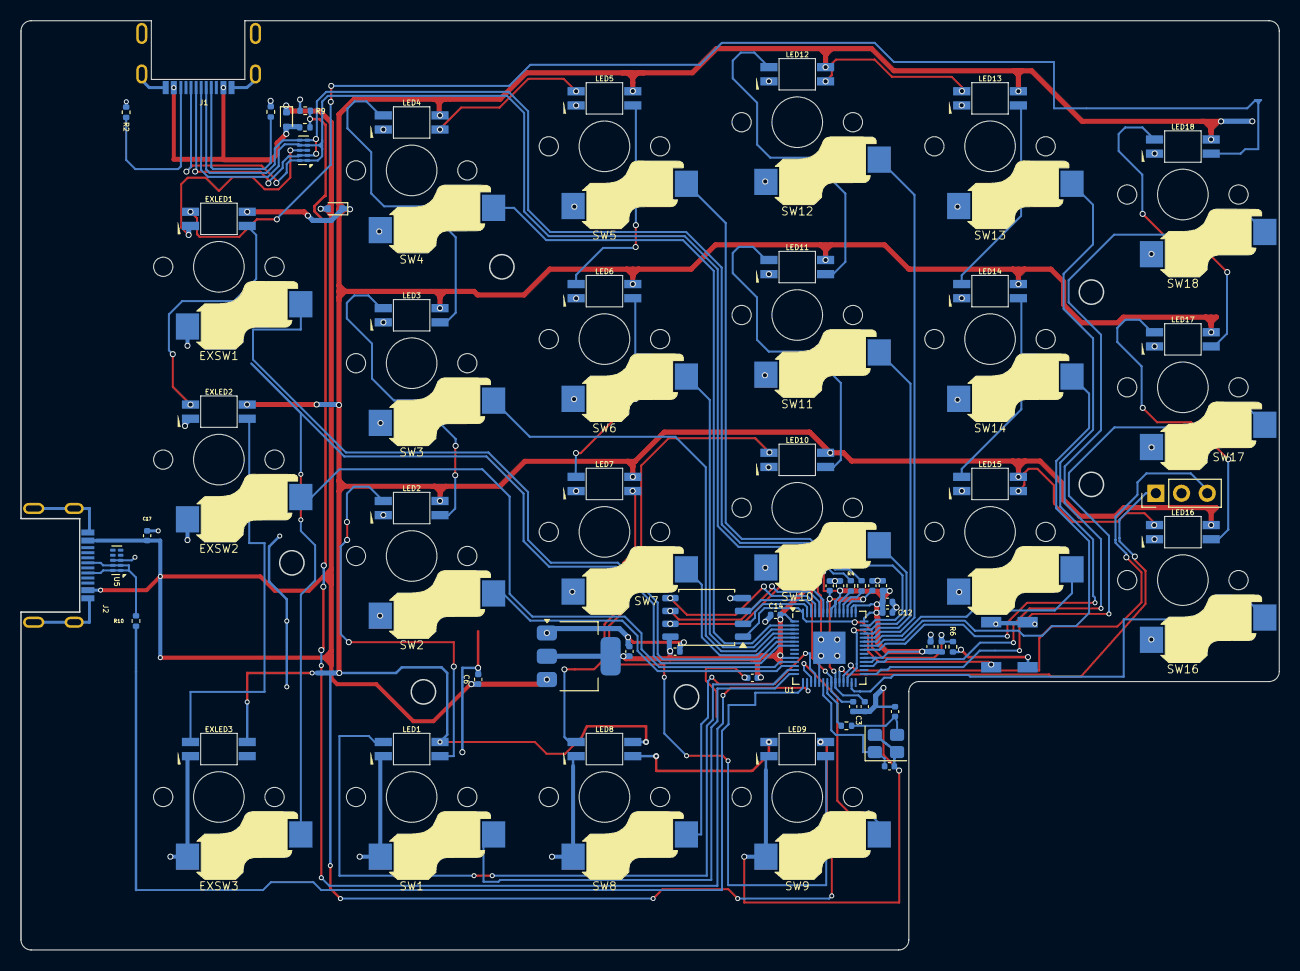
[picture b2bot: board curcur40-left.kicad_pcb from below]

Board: 2 copper layers, 124.3 x 91.8 mm, 82 parts (82 on the bottom side), 70 nets.

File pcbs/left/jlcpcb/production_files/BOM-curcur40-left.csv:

Comment,Designator,Footprint,LCSC
W25Q128JVSIQ,U4,SOIC-8_5.3x5.3mm_P1.27mm,C113767
1k,"R3,R6",R_0402_1005Metric,C11702
TPD4E05U06DQAR,"U3,U5",USON-10_2.5x1.0mm_P0.5mm,C138714
RB521S30T1G,ZD1,D_SOD-523,C145179
NCP1117LPST33T3G,U2,SOT-223-3_TabPin2,C146799
100n,"C10,C12,C13,C14,C15,C17,C3,C4,C7,C9",C_0402_1005Metric,C1525
10u,"C11,C6",C_0402_1005Metric,C15525
27p,"C1,C2",C_0402_1005Metric,C1557
RP2040,U1,QFN-56-1EP_7x7mm_P0.4mm_EP3.2x3.2mm,C2040
1N4148WT,D1,D_SOD-523,C232841
10k,"R7,R9",R_0402_1005Metric,C25744
5.1k,"R1,R2",R_0402_1005Metric,C25905
5.6k,R8,R_0402_1005Metric,C25908
TYPE-C-31-M-13C,"J1,J2",TYPE-C-31-M-13C,C2848620
27,"R10,R4,R5",R_0402_1005Metric,C2909343
TS-1088R-02026,"SMDSW1,SMDSW2",TS-1088R-02026,C455280
YS-SK6812MINI-E,"EXLED1,EXLED2,EXLED3,LED1,LED10,LED11,LED12,LED13,LED14,LED15,LED16,LED17,LED18,LED2,LED3,LED4,LED5,LED6,LED7,LED8,LED9",YS-SK6812MINI-E,C5149201
1u,"C16,C5,C8",C_0402_1005Metric,C52923
SW_Push,"EXSW1,EXSW2,EXSW3,SW1,SW10,SW11,SW12,SW13,SW14,SW15,SW16,SW17,SW18,SW2,SW3,SW4,SW5,SW6,SW7,SW8,SW9",keyswitch_choc12_hotswap_1u,C5333465
12MHz 18pF,Y1,Crystal_SMD_3225-4Pin_3.2x2.5mm,C91749

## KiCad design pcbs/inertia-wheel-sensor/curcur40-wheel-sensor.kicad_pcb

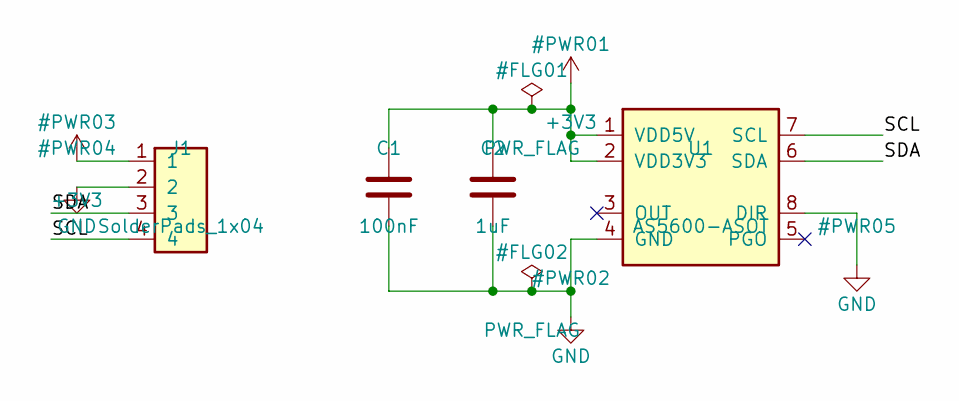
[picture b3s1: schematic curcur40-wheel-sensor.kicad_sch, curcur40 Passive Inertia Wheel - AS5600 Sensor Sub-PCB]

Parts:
C1: 100nF; C_0402_1005Metric; LCSC C1525
C2: 1uF; C_0402_1005Metric; LCSC C52923
J1: SolderPads_1x04; SolderPads_1x04_P1.27mm_SMD
U1: AS5600-ASOT; SOIC-8_3.9x4.9mm_P1.27mm; LCSC C499458

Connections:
+3V3: C1.1, C2.1, J1.1, U1.1 (VDD5V), U1.2 (VDD3V3)
/SCL: J1.4, U1.7 (SCL)
/SDA: J1.3, U1.6 (SDA)
GND: C1.2, C2.2, J1.2, U1.4 (GND), U1.8 (DIR)

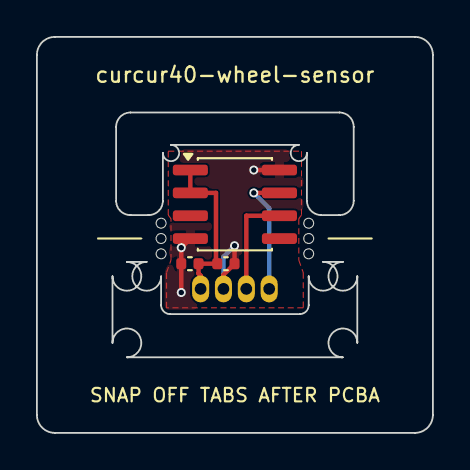
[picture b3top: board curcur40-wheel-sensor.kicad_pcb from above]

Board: 2 copper layers, 22.0 x 22.0 mm, 6 parts (0 on the bottom side), 4 nets.

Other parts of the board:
MB1, MB2: MouseBite; MouseBite_3x0.55mm

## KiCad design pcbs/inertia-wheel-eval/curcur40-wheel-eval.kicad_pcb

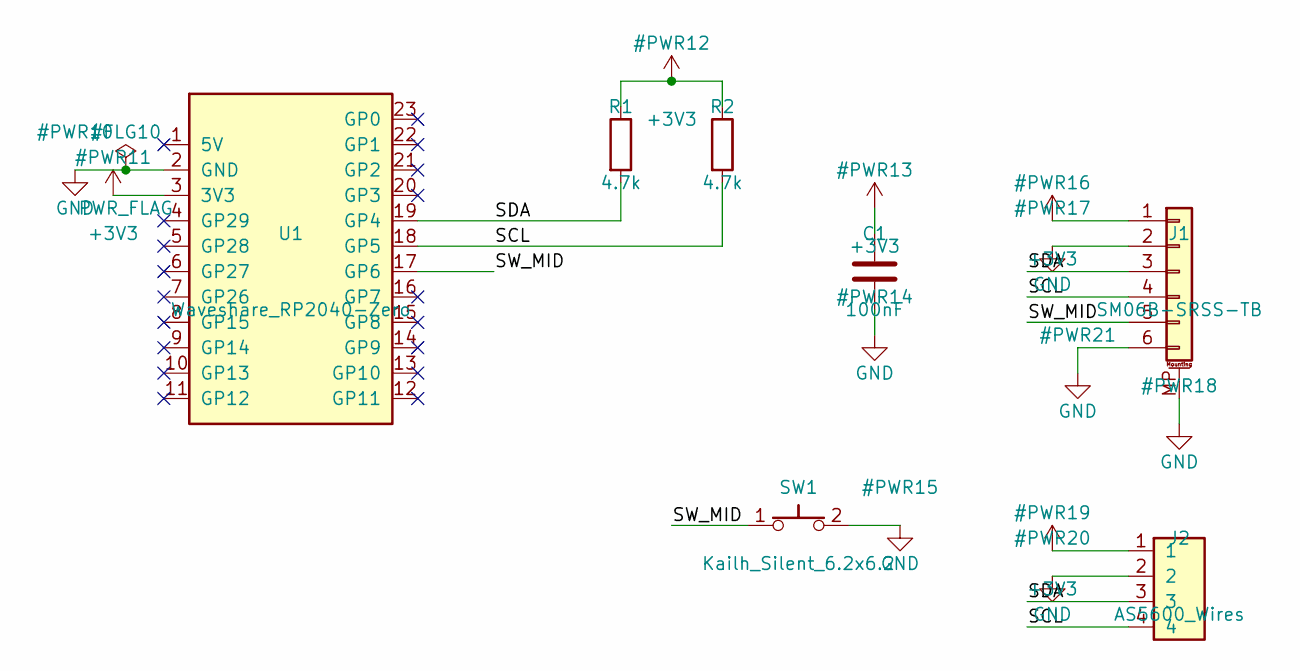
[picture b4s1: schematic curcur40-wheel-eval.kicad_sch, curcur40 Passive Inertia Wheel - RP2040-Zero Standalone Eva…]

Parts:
C1: 100nF; C_0402_1005Metric; LCSC C1525
J1: SM06B-SRSS-TB; JST_SH_SM06B-SRSS-TB_1x06-1MP_P1.00mm_Horizontal; LCSC C160405
J2: AS5600_Wires; SolderPads_1x04_P1.27mm_SMD
R1, R2: 4.7k; R_0402_1005Metric; LCSC C25900
SW1: Kailh_Silent_6.2x6.2; Kailh_Square_Silent_6.2x6.2mm
U1: Waveshare_RP2040-Zero; Waveshare_RP2040-Zero_Castellated

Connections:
+3V3: C1.1, J1.1, J2.1, R1.1, R2.1, U1.3 (3V3)
/SCL: J1.4, J2.4, R2.2, U1.18 (GP5)
/SDA: J1.3, J2.3, R1.2, U1.19 (GP4)
/SW_MID: J1.5, SW1.1, U1.17 (GP6)
GND: C1.2, J1.2, J1.6, J1.MP (MountPin), J2.2, SW1.2, U1.2 (GND)

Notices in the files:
pcbs/curcur40/pmw3360/curcur40-pmw3360.kicad_pcb:
Open Source Hardware, CERN-OHL-P v2
